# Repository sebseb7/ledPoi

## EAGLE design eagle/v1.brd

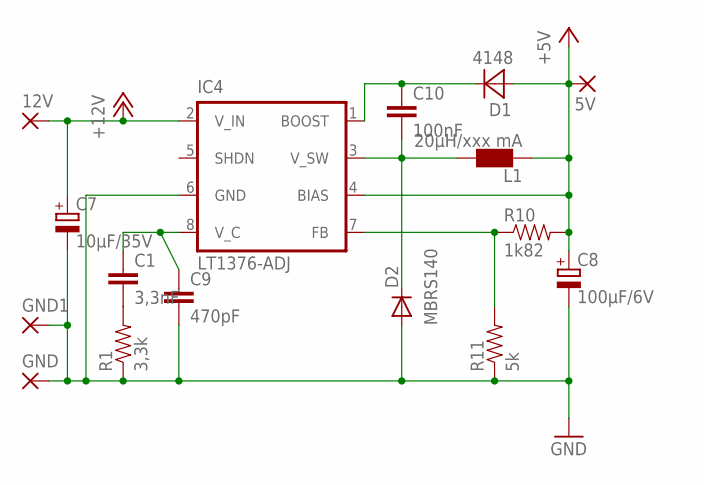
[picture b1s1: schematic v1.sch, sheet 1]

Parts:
5V, 12V: SMD5; SMD2,54-5,08
C1: 3,3nF; 0805
C7: 10µF/35V; SMC_D
C8: 100µF/6V; SMC_D
C9: 470pF; 0805
C10: 100nF; 0805
D1: 4148; DIODE_0805
D2: MBRS140; SMB
GND, GND1: SMD5; SMD2,54-5,08
IC4: LT1376-ADJ; SO-08
L1: 20µH/xxx mA; PIS2408
R1: 3,3k; 0805
R10: 1k82; 0805
R11: 5k; 0805

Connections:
+5V: 5V.1, C8.+, D1.2 (A), IC4.4 (BIAS), L1.P$2 (2), R10.2; also elsewhere on the board
+12V: 12V.1, C7.+, IC4.2 (V_IN); also elsewhere on the board
GND: C7.-, C8.-, C9.2, D2.A, GND.1, GND1.1, IC4.6 (GND), R1.1, R11.1; also elsewhere on the board
unnamed: C1.2, R1.2
unnamed: IC4.7 (FB), R10.1, R11.2
unnamed: C1.1, C9.1, IC4.8 (V_C)
unnamed: C10.2, D2.C, IC4.3 (V_SW), L1.P$1 (1)
unnamed: C10.1, D1.1 (C), IC4.1 (BOOST)

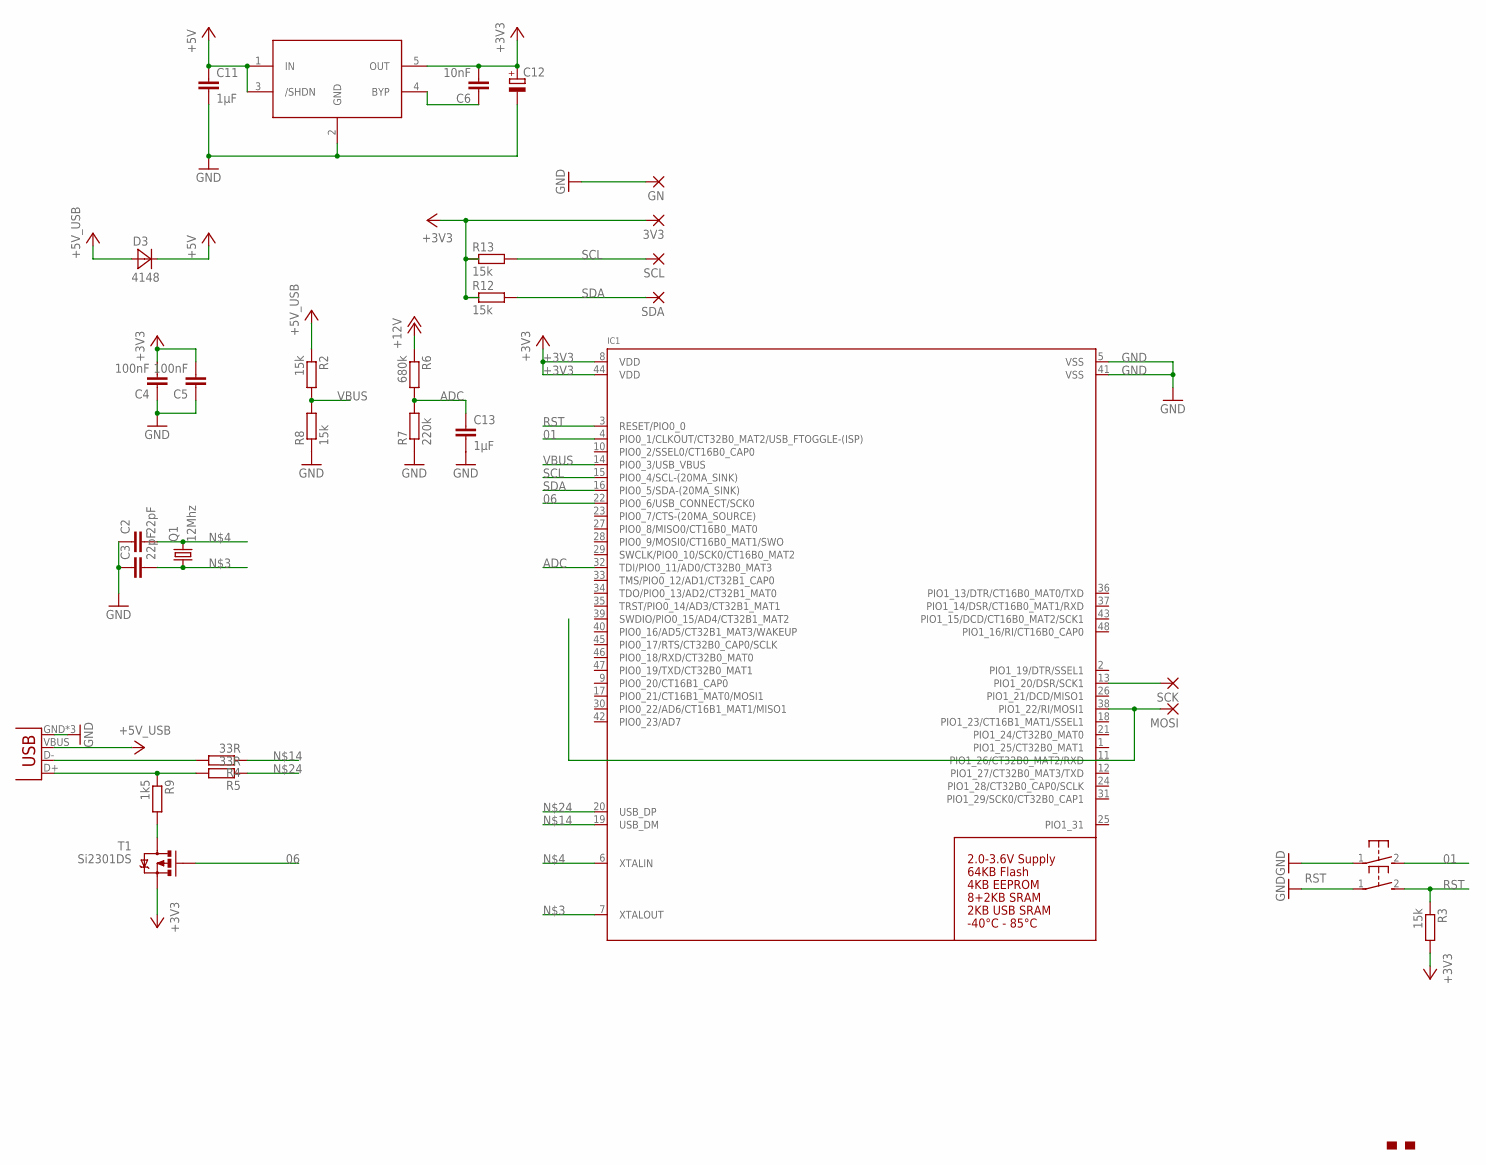
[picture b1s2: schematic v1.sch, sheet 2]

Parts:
3V3: SMD2; SMD1,27-2,54
BL: SWITCH_MCTAEF
C2, C3: 22pF; C0402
C4, C5: 100nF; C0402
C6: 10nF; C0402
C11, C13: 1µF; 0805
C12: CPOL-EUSMCA; SMC_A
D3: 4148; DIODE_0805
GN: SMD2; SMD1,27-2,54
IC1: LPC1347_QFP48; LQFP48
IC2: LT1761; SOT23-5L
MOSI: SMD5; SMD2,54-5,08
Q1: 12Mhz; MT
R2, R3, R8, R12, R13: 15k; R0402
R4, R5: 33R; R0402
R6: 680k; R0402
R7: 220k; R0402
R9: 1k5; R0402
RST: SWITCH_MCTAEF
SCK: SMD5; SMD2,54-5,08
SCL: SMD2; SMD1,27-2,54
SDA: SMD2; SMD1,27-2,54
T1: Si2301DS; SOT23
U$1: MAKE-DD_LOGO'PROMPT'; MAKE-DD_LOGO_PROMPT
X1: USB-MICROB

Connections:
01: BL.2, IC1.4 (PIO0_1/CLKOUT/CT32B0_MAT2/USB_FTOGGLE-(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)
06: IC1.22 (PIO0_6/USB_CONNECT/SCK0), T1.1 (G)
+3V3: 3V3.1, C4.2, C5.2, C6.2, C12.+, IC1.8 (VDD), IC1.44 (VDD), IC2.5 (OUT), R3.2, R12.1, R13.1, T1.2 (S)
+5V: C11.1, D3.1 (C), IC2.1 (IN), IC2.3 (/SHDN); also elsewhere on the board
+5V_USB: D3.2 (A), R2.1, X1.VBUS
+12V: R6.1; also elsewhere on the board
ADC: C13.1, IC1.32 (TDI/PIO0_11/AD0/CT32B0_MAT3), R6.2, R7.2
GND: BL.1, C2.1, C3.1, C4.1, C5.1, C11.2, C12.-, C13.2, GN.1, IC1.5 (VSS), IC1.41 (VSS), IC2.2 (GND), R7.1, R8.1, RST.1, X1.GND, X1.MT1 (GND), X1.MT2 (GND); also elsewhere on the board
unnamed: R5.2, R9.1, X1.D+
unnamed: C3.2, IC1.7 (XTALOUT), Q1.1
unnamed: C2.2, IC1.6 (XTALIN), Q1.3 (2)
unnamed: C6.1, IC2.4 (BYP)
unnamed: IC1.13 (PIO1_20/DSR/SCK1), SCK.1
unnamed: IC1.38 (PIO1_22/RI/MOSI1), MOSI.1
unnamed: R4.2, X1.D-
unnamed: IC1.19 (USB_DM), R4.1
unnamed: R9.2, T1.3 (D)
unnamed: IC1.20 (USB_DP), R5.1
RST: IC1.3 (RESET/PIO0_0), R3.1, RST.2
SCL: IC1.15 (PIO0_4/SCL-(20MA_SINK)), R13.2, SCL.1
SDA: IC1.16 (PIO0_5/SDA-(20MA_SINK)), R12.2, SDA.1
VBUS: IC1.14 (PIO0_3/USB_VBUS), R2.2, R8.2

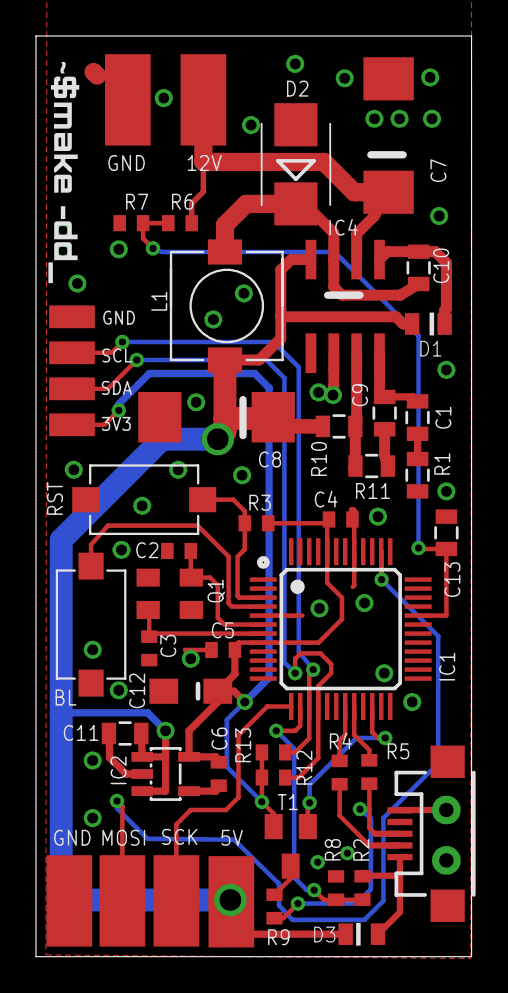
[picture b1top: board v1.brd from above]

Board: 2 copper layers, 24.2 x 51.2 mm, 49 parts (0 on the bottom side), 27 nets.

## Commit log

2013-06-18 initial version
2013-06-18 two minor layout fixes
2013-06-20 firmware template
2013-06-20 spi output working
2013-06-20 new function for sending single bytes
2013-06-20 first light, leds working
2013-06-20 ignorance
2013-06-20 led api & firmware directory
2013-06-20 fix last commit
2013-06-20 added simulator
2013-06-20 added first animation
2013-06-20 move header
2013-06-25 optimized connector layout
2013-06-25 faster
2013-06-25 new animation
2013-06-25 for testing rpm
2013-06-25 eliminate gcc warning
2013-06-26 make constructors work
2013-06-26 removed timing from tick
2013-06-26 double sided poi
2013-06-26 added animation support
2013-06-26 constructor support needs this
2013-06-26 cleanup
2013-06-26 ignore simulator binaries
2013-06-26 small change
2013-06-26 mege
2013-06-26 i2c connector
2013-06-26 final touches for production run
2013-06-27 improved simulator preceision
2013-06-27 updated animations
2013-06-27 led arrangement for new led stripe
2013-06-27 updated animation set
2013-06-27 support for shared libs
2013-06-27 shared lib: 7x5 font
2013-06-27 text demo
2013-06-27 more realistic
2013-07-02 turned usb
2013-07-02 arrows
2013-07-02 wider
2013-07-03 new animations
2013-09-06 gaggalacka!
2013-09-06 add voltage display
2013-09-06 reduced binary size
2013-09-06 warning
2013-09-06 sim fix & cleanup
2013-09-06 refinements
2014-06-23 supply circuit via USB for firmware upgrades
2015-10-20 merge
2015-10-20 eagle update
2015-10-31 gcc fix
2015-10-31 non osx fix
2015-10-31 voltage 2

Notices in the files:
parts and their libraries:
SparkFun-Connectors: Licensing: CC v3.0 Share-Alike You are welcome to use this library for commercial purposes.
